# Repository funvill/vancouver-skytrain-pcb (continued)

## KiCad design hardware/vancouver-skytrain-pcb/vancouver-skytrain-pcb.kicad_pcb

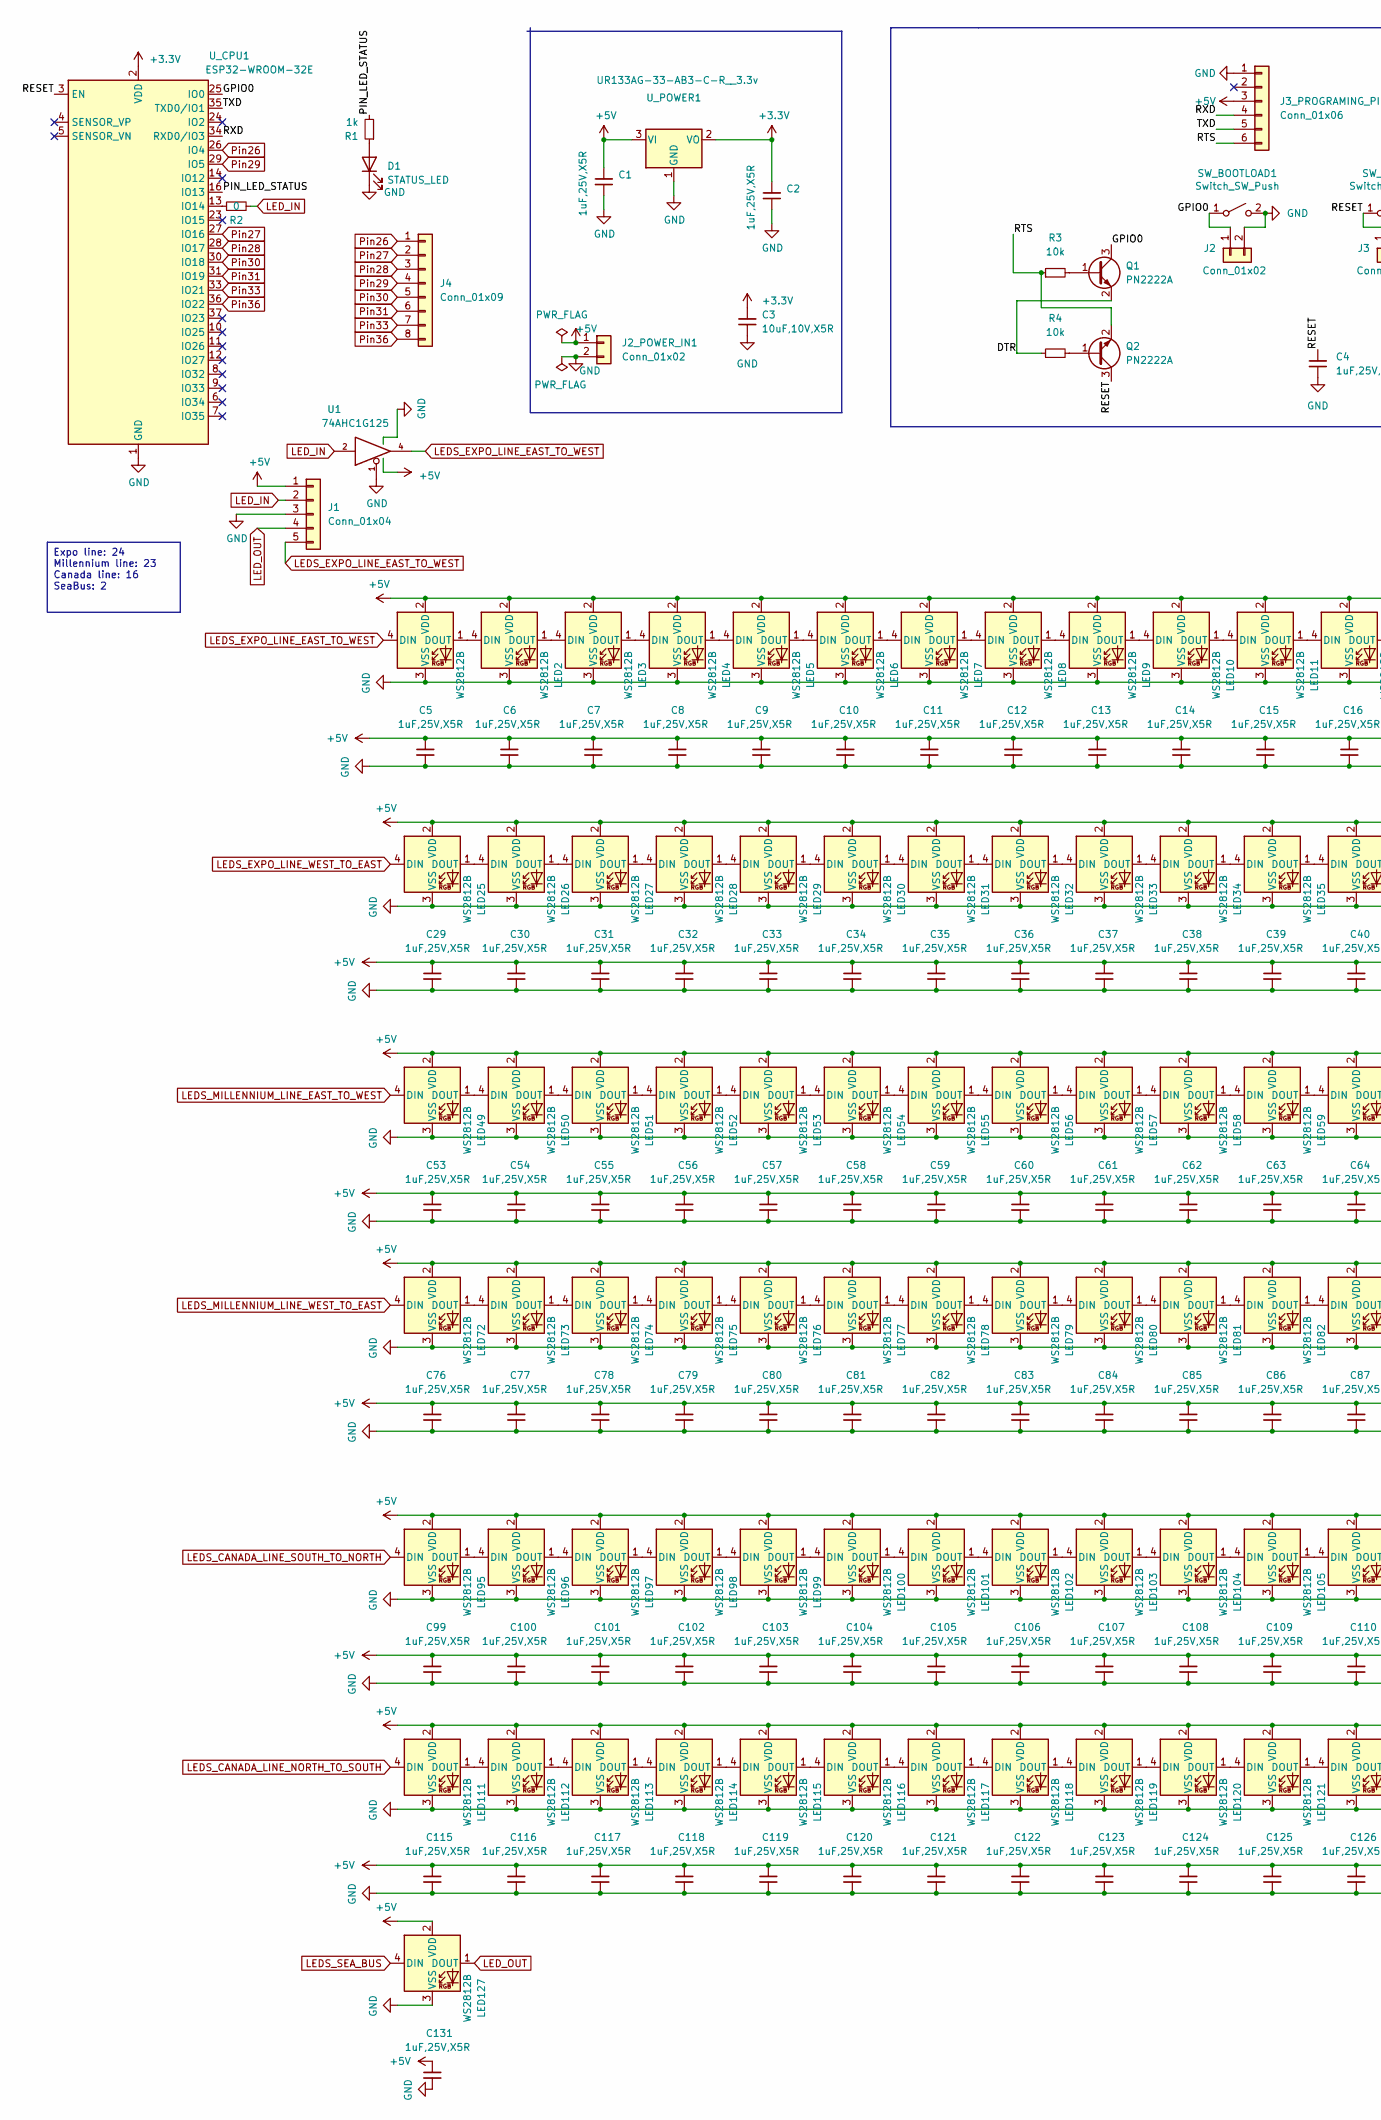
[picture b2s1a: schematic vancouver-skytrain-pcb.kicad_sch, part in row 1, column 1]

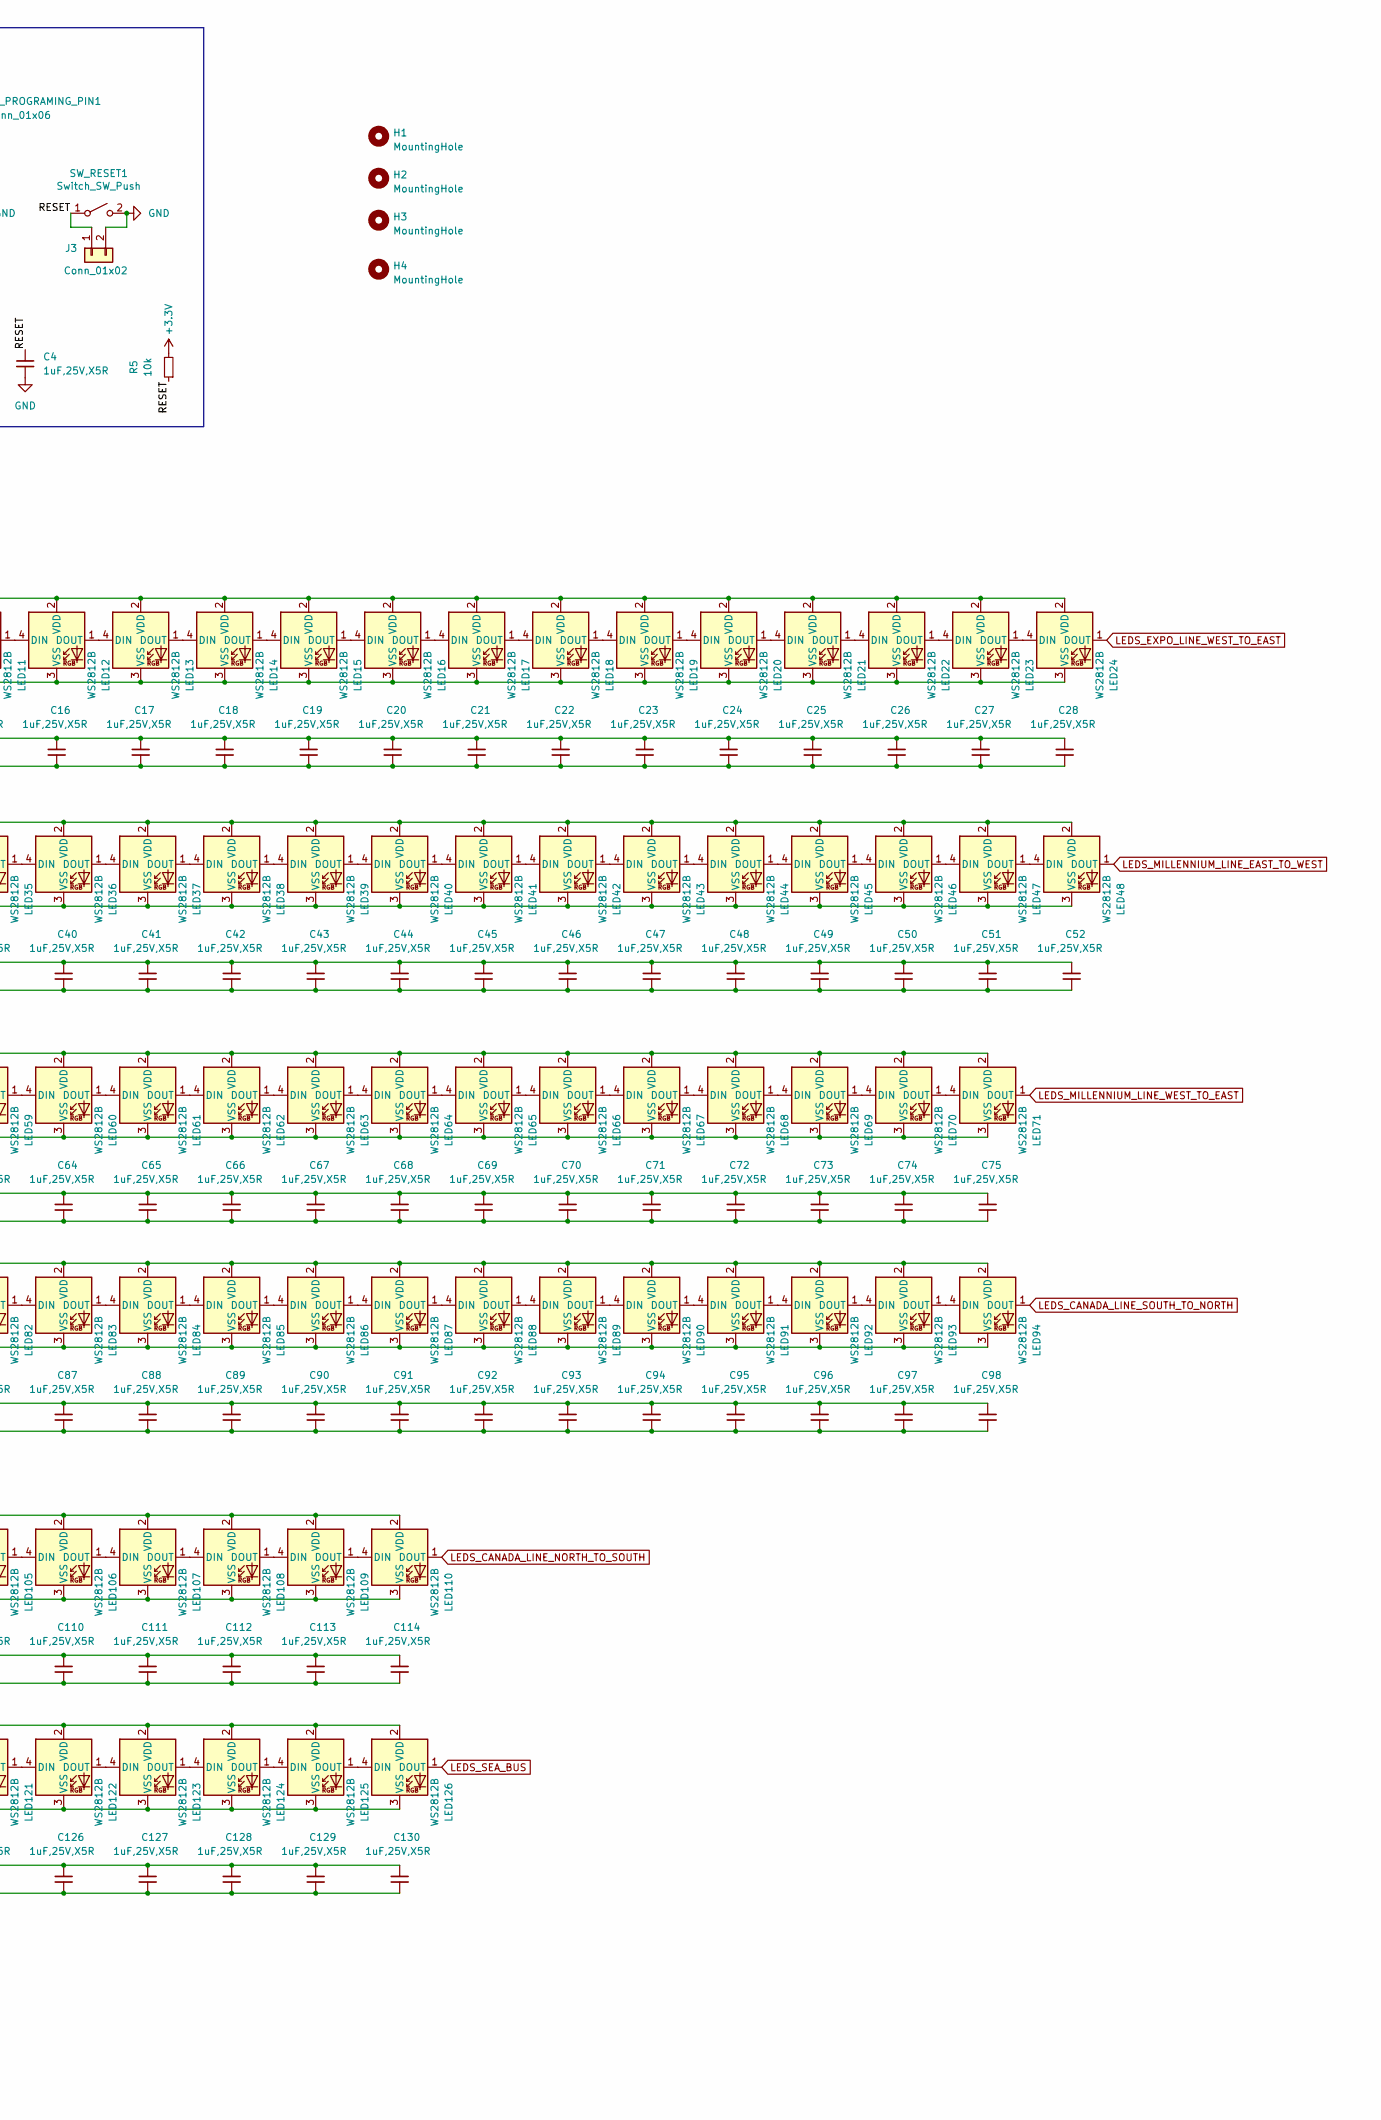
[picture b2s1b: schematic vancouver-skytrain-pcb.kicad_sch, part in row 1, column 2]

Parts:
C1, C2, C4, C5, C6, C7, C8, C9, C10, C11, C12, C13, C14, C15, C16, C17, C18, C19, C20, C21, C22, C23, C24, C25, C26, C27, C28, C29, C30, C31, C32, C33, C34, C35, C36, C37, C38, C39, C40, C41, C42, C43, C44, C45, C46, C47, C48, C49, C50, C51, C52, C53, C54, C55, C56, C57, C58, C59, C60, C61, C62, C63, C64, C65, C66, C67, C68, C69, C70, C71, C72, C73, C74, C75, C76, C77, C78, C79, C80, C81, C82, C83, C84, C85, C86, C87, C88, C89, C90, C91, C92, C93, C94, C95, C96, C97, C98, C99, C100, C101, C102, C103, C104, C105, C106, C107, C108, C109, C110, C111, C112, C113, C114, C115, C116, C117, C118, C119, C120, C121, C122, C123, C124, C125, C126, C127, C128, C129, C130, C131: 1uF,25V,X5R; C_0402_1005Metric; MFGPN CL05A105KA5NQNC; LCSC C52923
C3: 10uF,10V,X5R; C_0603_1608Metric; MFGPN CL10A106KP8NNNC; LCSC C19702
D1: STATUS_LED; LED_0603_1608Metric; LCSC C2286
H1, H2, H3, H4: MountingHole; MountingHole_3.2mm_M3
J1: Conn_01x04; PinHeader_1x05_P2.54mm_Vertical
J2, J3: Conn_01x02; PinHeader_1x02_P2.54mm_Vertical
J2_POWER_IN1: Conn_01x02; PhoenixContact_MCV_1,5_2-G-3.81_1x02_P3.81mm_Vertical
J3_PROGRAMING_PIN1: Conn_01x06; PinHeader_1x06_P2.54mm_Vertical
J4: Conn_01x09; PinHeader_1x08_P2.54mm_Vertical
LED1, LED2, LED3, LED4, LED5, LED6, LED7, LED8, LED9, LED10, LED11, LED12, LED13, LED14, LED15, LED16, LED17, LED18, LED19, LED20, LED21, LED22, LED23, LED24, LED25, LED26, LED27, LED28, LED29, LED30, LED31, LED32, LED33, LED34, LED35, LED36, LED37, LED38, LED39, LED40, LED41, LED42, LED43, LED44, LED45, LED46, LED47, LED48, LED49, LED50, LED51, LED52, LED53, LED54, LED55, LED56, LED57, LED58, LED59, LED60, LED61, LED62, LED63, LED64, LED65, LED66, LED67, LED68, LED69, LED70, LED71, LED72, LED73, LED74, LED75, LED76, LED77, LED78, LED79, LED80, LED81, LED82, LED83, LED84, LED85, LED86, LED87, LED88, LED89, LED90, LED91, LED92, LED93, LED94, LED95, LED96, LED97, LED98, LED99, LED100, LED101, LED102, LED103, LED104, LED105, LED106, LED107, LED108, LED109, LED110, LED111, LED112, LED113, LED114, LED115, LED116, LED117, LED118, LED119, LED120, LED121, LED122, LED123, LED124, LED125, LED126, LED127: WS2812B; XL-1010RGBC-WS2812B; LCSC C5349953
Q1, Q2: PN2222A; SOT-416; LCSC C242260
R1: 1k; C_0402_1005Metric; MFGPN 0402WGF1001TCE; LCSC C11702
R2: 0; R_0402_1005Metric; MFGPN 0402WGF0000TCE; LCSC C17168
R3, R4, R5: 10k; C_0402_1005Metric; MFGPN 0402WGF1002TCE; LCSC C25744
SW_BOOTLOAD1: Switch_SW_Push; SW_Push_1P1T_NO_6x6mm_H9.5mm; LCSC DNP
SW_RESET1: Switch_SW_Push; SW_Push_1P1T_NO_6x6mm_H9.5mm; LCSC DNP
U1: 74AHC1G125; SOT-23-5; LCSC C23654
U_CPU1: ESP32-WROOM-32E; ESP32-WROOM-32; LCSC C701342
U_POWER1: UR133AG-33-AB3-C-R__3.3v; SOT-89-3; LCSC C73288

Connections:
+3.3V: C2.1, C3.1, R5.2, U_CPU1.2 (VDD), U_POWER1.2 (VO)
+5V: C1.1, C5.1, C6.1, C7.1, C8.1, C9.1, C10.1, C11.1, C12.1, C13.1, C14.1, C15.1, C16.1, C17.1, C18.1, C19.1, C20.1, C21.1, C22.1, C23.1, C24.1, C25.1, C26.1, C27.1, C28.1, C29.1, C30.1, C31.1, C32.1, C33.1, C34.1, C35.1, C36.1, C37.1, C38.1, C39.1, C40.1, C41.1, C42.1, C43.1, C44.1, C45.1, C46.1, C47.1, C48.1, C49.1, C50.1, C51.1, C52.1, C53.1, C54.1, C55.1, C56.1, C57.1, C58.1, C59.1, C60.1, C61.1, C62.1, C63.1, C64.1, C65.1, C66.1, C67.1, C68.1, C69.1, C70.1, C71.1, C72.1, C73.1, C74.1, C75.1, C76.1, C77.1, C78.1, C79.1, C80.1, C81.1, C82.1, C83.1, C84.1, C85.1, C86.1, C87.1, C88.1, C89.1, C90.1, C91.1, C92.1, C93.1, C94.1, C95.1, C96.1, C97.1, C98.1, C99.1, C100.1, C101.1, C102.1, C103.1, C104.1, C105.1, C106.1, C107.1, C108.1, C109.1, C110.1, C111.1, C112.1, C113.1, C114.1, C115.1, C116.1, C117.1, C118.1, C119.1, C120.1, C121.1, C122.1, C123.1, C124.1, C125.1, C126.1, C127.1, C128.1, C129.1, C130.1, C131.1, J1.1, J2_POWER_IN1.1, J3_PROGRAMING_PIN1.3, LED1.2 (VDD), LED2.2 (VDD), LED3.2 (VDD), LED4.2 (VDD), LED5.2 (VDD), LED6.2 (VDD), LED7.2 (VDD), LED8.2 (VDD), LED9.2 (VDD), LED10.2 (VDD), LED11.2 (VDD), LED12.2 (VDD), LED13.2 (VDD), LED14.2 (VDD), LED15.2 (VDD), LED16.2 (VDD), LED17.2 (VDD), LED18.2 (VDD), LED19.2 (VDD), LED20.2 (VDD), LED21.2 (VDD), LED22.2 (VDD), LED23.2 (VDD), LED24.2 (VDD), LED25.2 (VDD), LED26.2 (VDD), LED27.2 (VDD), LED28.2 (VDD), LED29.2 (VDD), LED30.2 (VDD), LED31.2 (VDD), LED32.2 (VDD), LED33.2 (VDD), LED34.2 (VDD), LED35.2 (VDD), LED36.2 (VDD), LED37.2 (VDD), LED38.2 (VDD), LED39.2 (VDD), LED40.2 (VDD), LED41.2 (VDD), LED42.2 (VDD), LED43.2 (VDD), LED44.2 (VDD), LED45.2 (VDD), LED46.2 (VDD), LED47.2 (VDD), LED48.2 (VDD), LED49.2 (VDD), LED50.2 (VDD), LED51.2 (VDD), LED52.2 (VDD), LED53.2 (VDD), LED54.2 (VDD), LED55.2 (VDD), LED56.2 (VDD), LED57.2 (VDD), LED58.2 (VDD), LED59.2 (VDD), LED60.2 (VDD), LED61.2 (VDD), LED62.2 (VDD), LED63.2 (VDD), LED64.2 (VDD), LED65.2 (VDD), LED66.2 (VDD), LED67.2 (VDD), LED68.2 (VDD), LED69.2 (VDD), LED70.2 (VDD), LED71.2 (VDD), LED72.2 (VDD), LED73.2 (VDD), LED74.2 (VDD), LED75.2 (VDD), LED76.2 (VDD), LED77.2 (VDD), LED78.2 (VDD), LED79.2 (VDD), LED80.2 (VDD), LED81.2 (VDD), LED82.2 (VDD), LED83.2 (VDD), LED84.2 (VDD), LED85.2 (VDD), LED86.2 (VDD), LED87.2 (VDD), LED88.2 (VDD), LED89.2 (VDD), LED90.2 (VDD), LED91.2 (VDD), LED92.2 (VDD), LED93.2 (VDD), LED94.2 (VDD), LED95.2 (VDD), LED96.2 (VDD), LED97.2 (VDD), LED98.2 (VDD), LED99.2 (VDD), LED100.2 (VDD), LED101.2 (VDD), LED102.2 (VDD), LED103.2 (VDD), LED104.2 (VDD), LED105.2 (VDD), LED106.2 (VDD), LED107.2 (VDD), LED108.2 (VDD), LED109.2 (VDD), LED110.2 (VDD), LED111.2 (VDD), LED112.2 (VDD), LED113.2 (VDD), LED114.2 (VDD), LED115.2 (VDD), LED116.2 (VDD), LED117.2 (VDD), LED118.2 (VDD), LED119.2 (VDD), LED120.2 (VDD), LED121.2 (VDD), LED122.2 (VDD), LED123.2 (VDD), LED124.2 (VDD), LED125.2 (VDD), LED126.2 (VDD), LED127.2 (VDD), U1.5 (VCC), U_POWER1.3 (VI); also elsewhere on the board
/DTR: Q1.2 (E), R4.1
/GPIO0: J2.1, Q1.3 (C), SW_BOOTLOAD1.1 (A), U_CPU1.25 (IO0)
/PIN_LED_STATUS: R1.2, U_CPU1.16 (IO13)
/RESET: C4.1, J3.1, Q2.3 (C), R5.1, SW_RESET1.1 (A), U_CPU1.3 (EN)
/RTS: J3_PROGRAMING_PIN1.6, Q2.2 (E), R3.1
/RXD: J3_PROGRAMING_PIN1.4, U_CPU1.34 (RXD0/IO3)
/TXD: J3_PROGRAMING_PIN1.5, U_CPU1.35 (TXD0/IO1)
GND: C1.2, C2.2, C3.2, C4.2, C5.2, C6.2, C7.2, C8.2, C9.2, C10.2, C11.2, C12.2, C13.2, C14.2, C15.2, C16.2, C17.2, C18.2, C19.2, C20.2, C21.2, C22.2, C23.2, C24.2, C25.2, C26.2, C27.2, C28.2, C29.2, C30.2, C31.2, C32.2, C33.2, C34.2, C35.2, C36.2, C37.2, C38.2, C39.2, C40.2, C41.2, C42.2, C43.2, C44.2, C45.2, C46.2, C47.2, C48.2, C49.2, C50.2, C51.2, C52.2, C53.2, C54.2, C55.2, C56.2, C57.2, C58.2, C59.2, C60.2, C61.2, C62.2, C63.2, C64.2, C65.2, C66.2, C67.2, C68.2, C69.2, C70.2, C71.2, C72.2, C73.2, C74.2, C75.2, C76.2, C77.2, C78.2, C79.2, C80.2, C81.2, C82.2, C83.2, C84.2, C85.2, C86.2, C87.2, C88.2, C89.2, C90.2, C91.2, C92.2, C93.2, C94.2, C95.2, C96.2, C97.2, C98.2, C99.2, C100.2, C101.2, C102.2, C103.2, C104.2, C105.2, C106.2, C107.2, C108.2, C109.2, C110.2, C111.2, C112.2, C113.2, C114.2, C115.2, C116.2, C117.2, C118.2, C119.2, C120.2, C121.2, C122.2, C123.2, C124.2, C125.2, C126.2, C127.2, C128.2, C129.2, C130.2, C131.2, D1.1 (K), J1.3, J2.2, J2_POWER_IN1.2, J3.2, J3_PROGRAMING_PIN1.1, LED1.3 (VSS), LED2.3 (VSS), LED3.3 (VSS), LED4.3 (VSS), LED5.3 (VSS), LED6.3 (VSS), LED7.3 (VSS), LED8.3 (VSS), LED9.3 (VSS), LED10.3 (VSS), LED11.3 (VSS), LED12.3 (VSS), LED13.3 (VSS), LED14.3 (VSS), LED15.3 (VSS), LED16.3 (VSS), LED17.3 (VSS), LED18.3 (VSS), LED19.3 (VSS), LED20.3 (VSS), LED21.3 (VSS), LED22.3 (VSS), LED23.3 (VSS), LED24.3 (VSS), LED25.3 (VSS), LED26.3 (VSS), LED27.3 (VSS), LED28.3 (VSS), LED29.3 (VSS), LED30.3 (VSS), LED31.3 (VSS), LED32.3 (VSS), LED33.3 (VSS), LED34.3 (VSS), LED35.3 (VSS), LED36.3 (VSS), LED37.3 (VSS), LED38.3 (VSS), LED39.3 (VSS), LED40.3 (VSS), LED41.3 (VSS), LED42.3 (VSS), LED43.3 (VSS), LED44.3 (VSS), LED45.3 (VSS), LED46.3 (VSS), LED47.3 (VSS), LED48.3 (VSS), LED49.3 (VSS), LED50.3 (VSS), LED51.3 (VSS), LED52.3 (VSS), LED53.3 (VSS), LED54.3 (VSS), LED55.3 (VSS), LED56.3 (VSS), LED57.3 (VSS), LED58.3 (VSS), LED59.3 (VSS), LED60.3 (VSS), LED61.3 (VSS), LED62.3 (VSS), LED63.3 (VSS), LED64.3 (VSS), LED65.3 (VSS), LED66.3 (VSS), LED67.3 (VSS), LED68.3 (VSS), LED69.3 (VSS), LED70.3 (VSS), LED71.3 (VSS), LED72.3 (VSS), LED73.3 (VSS), LED74.3 (VSS), LED75.3 (VSS), LED76.3 (VSS), LED77.3 (VSS), LED78.3 (VSS), LED79.3 (VSS), LED80.3 (VSS), LED81.3 (VSS), LED82.3 (VSS), LED83.3 (VSS), LED84.3 (VSS), LED85.3 (VSS), LED86.3 (VSS), LED87.3 (VSS), LED88.3 (VSS), LED89.3 (VSS), LED90.3 (VSS), LED91.3 (VSS), LED92.3 (VSS), LED93.3 (VSS), LED94.3 (VSS), LED95.3 (VSS), LED96.3 (VSS), LED97.3 (VSS), LED98.3 (VSS), LED99.3 (VSS), LED100.3 (VSS), LED101.3 (VSS), LED102.3 (VSS), LED103.3 (VSS), LED104.3 (VSS), LED105.3 (VSS), LED106.3 (VSS), LED107.3 (VSS), LED108.3 (VSS), LED109.3 (VSS), LED110.3 (VSS), LED111.3 (VSS), LED112.3 (VSS), LED113.3 (VSS), LED114.3 (VSS), LED115.3 (VSS), LED116.3 (VSS), LED117.3 (VSS), LED118.3 (VSS), LED119.3 (VSS), LED120.3 (VSS), LED121.3 (VSS), LED122.3 (VSS), LED123.3 (VSS), LED124.3 (VSS), LED125.3 (VSS), LED126.3 (VSS), LED127.3 (VSS), SW_BOOTLOAD1.2 (B), SW_RESET1.2 (B), U1.1, U1.3 (GND), U_CPU1.1 (GND), U_CPU1.15 (GND), U_CPU1.38 (GND), U_CPU1.39 (GND), U_POWER1.1 (GND); also elsewhere on the board
LEDS_CANADA_LINE_NORTH_TO_SOUTH: LED110.1 (DOUT), LED111.4 (DIN)
LEDS_CANADA_LINE_SOUTH_TO_NORTH: LED94.1 (DOUT), LED95.4 (DIN)
LEDS_EXPO_LINE_EAST_TO_WEST: J1.5, LED1.4 (DIN), U1.4
LEDS_EXPO_LINE_WEST_TO_EAST: LED24.1 (DOUT), LED25.4 (DIN)
LEDS_MILLENNIUM_LINE_EAST_TO_WEST: LED48.1 (DOUT), LED49.4 (DIN)
LEDS_MILLENNIUM_LINE_WEST_TO_EAST: LED71.1 (DOUT), LED72.4 (DIN)
LEDS_SEA_BUS: LED126.1 (DOUT), LED127.4 (DIN)
LED_IN: J1.2, R2.2, U1.2
LED_OUT: J1.4, LED127.1 (DOUT)
unnamed: D1.2 (A), R1.1
unnamed: LED1.1 (DOUT), LED2.4 (DIN)
unnamed: LED2.1 (DOUT), LED3.4 (DIN)
unnamed: LED3.1 (DOUT), LED4.4 (DIN)
unnamed: LED4.1 (DOUT), LED5.4 (DIN)
unnamed: LED5.1 (DOUT), LED6.4 (DIN)
unnamed: LED6.1 (DOUT), LED7.4 (DIN)
unnamed: LED7.1 (DOUT), LED8.4 (DIN)
unnamed: LED8.1 (DOUT), LED9.4 (DIN)
unnamed: LED9.1 (DOUT), LED10.4 (DIN)
unnamed: LED10.1 (DOUT), LED11.4 (DIN)
unnamed: LED11.1 (DOUT), LED12.4 (DIN)
unnamed: LED12.1 (DOUT), LED13.4 (DIN)
unnamed: LED13.1 (DOUT), LED14.4 (DIN)
unnamed: LED14.1 (DOUT), LED15.4 (DIN)
unnamed: LED15.1 (DOUT), LED16.4 (DIN)
unnamed: LED16.1 (DOUT), LED17.4 (DIN)
unnamed: LED17.1 (DOUT), LED18.4 (DIN)
unnamed: LED18.1 (DOUT), LED19.4 (DIN)
unnamed: LED19.1 (DOUT), LED20.4 (DIN)
unnamed: LED20.1 (DOUT), LED21.4 (DIN)
unnamed: LED21.1 (DOUT), LED22.4 (DIN)
unnamed: LED22.1 (DOUT), LED23.4 (DIN)
unnamed: LED23.1 (DOUT), LED24.4 (DIN)
unnamed: LED25.1 (DOUT), LED26.4 (DIN)
unnamed: LED26.1 (DOUT), LED27.4 (DIN)
unnamed: LED27.1 (DOUT), LED28.4 (DIN)
unnamed: LED28.1 (DOUT), LED29.4 (DIN)
unnamed: LED29.1 (DOUT), LED30.4 (DIN)
unnamed: LED30.1 (DOUT), LED31.4 (DIN)
unnamed: LED31.1 (DOUT), LED32.4 (DIN)
unnamed: LED32.1 (DOUT), LED33.4 (DIN)
unnamed: LED33.1 (DOUT), LED34.4 (DIN)
unnamed: LED34.1 (DOUT), LED35.4 (DIN)
unnamed: LED35.1 (DOUT), LED36.4 (DIN)
unnamed: LED36.1 (DOUT), LED37.4 (DIN)
unnamed: LED37.1 (DOUT), LED38.4 (DIN)
unnamed: LED38.1 (DOUT), LED39.4 (DIN)
unnamed: LED39.1 (DOUT), LED40.4 (DIN)
unnamed: LED40.1 (DOUT), LED41.4 (DIN)
unnamed: LED41.1 (DOUT), LED42.4 (DIN)
unnamed: LED42.1 (DOUT), LED43.4 (DIN)
unnamed: LED43.1 (DOUT), LED44.4 (DIN)
unnamed: LED44.1 (DOUT), LED45.4 (DIN)
unnamed: LED45.1 (DOUT), LED46.4 (DIN)
unnamed: LED46.1 (DOUT), LED47.4 (DIN)
unnamed: LED47.1 (DOUT), LED48.4 (DIN)
unnamed: LED49.1 (DOUT), LED50.4 (DIN)
unnamed: LED50.1 (DOUT), LED51.4 (DIN)
unnamed: LED51.1 (DOUT), LED52.4 (DIN)
unnamed: LED52.1 (DOUT), LED53.4 (DIN)
unnamed: LED53.1 (DOUT), LED54.4 (DIN)
unnamed: LED54.1 (DOUT), LED55.4 (DIN)
unnamed: LED55.1 (DOUT), LED56.4 (DIN)
unnamed: LED56.1 (DOUT), LED57.4 (DIN)
unnamed: LED57.1 (DOUT), LED58.4 (DIN)
unnamed: LED58.1 (DOUT), LED59.4 (DIN)
unnamed: LED59.1 (DOUT), LED60.4 (DIN)
unnamed: LED60.1 (DOUT), LED61.4 (DIN)
unnamed: LED61.1 (DOUT), LED62.4 (DIN)
unnamed: LED62.1 (DOUT), LED63.4 (DIN)
unnamed: LED63.1 (DOUT), LED64.4 (DIN)
unnamed: LED64.1 (DOUT), LED65.4 (DIN)
unnamed: LED65.1 (DOUT), LED66.4 (DIN)
unnamed: LED66.1 (DOUT), LED67.4 (DIN)
unnamed: LED67.1 (DOUT), LED68.4 (DIN)
unnamed: LED68.1 (DOUT), LED69.4 (DIN)
unnamed: LED69.1 (DOUT), LED70.4 (DIN)
unnamed: LED70.1 (DOUT), LED71.4 (DIN)
unnamed: LED72.1 (DOUT), LED73.4 (DIN)
unnamed: LED73.1 (DOUT), LED74.4 (DIN)
unnamed: LED74.1 (DOUT), LED75.4 (DIN)
unnamed: LED75.1 (DOUT), LED76.4 (DIN)
unnamed: LED76.1 (DOUT), LED77.4 (DIN)
unnamed: LED77.1 (DOUT), LED78.4 (DIN)
unnamed: LED78.1 (DOUT), LED79.4 (DIN)
unnamed: LED79.1 (DOUT), LED80.4 (DIN)
unnamed: LED80.1 (DOUT), LED81.4 (DIN)
unnamed: LED81.1 (DOUT), LED82.4 (DIN)
unnamed: LED82.1 (DOUT), LED83.4 (DIN)
unnamed: LED83.1 (DOUT), LED84.4 (DIN)
unnamed: LED84.1 (DOUT), LED85.4 (DIN)
unnamed: LED85.1 (DOUT), LED86.4 (DIN)
unnamed: LED86.1 (DOUT), LED87.4 (DIN)
unnamed: LED87.1 (DOUT), LED88.4 (DIN)
unnamed: LED88.1 (DOUT), LED89.4 (DIN)
unnamed: LED89.1 (DOUT), LED90.4 (DIN)
unnamed: LED90.1 (DOUT), LED91.4 (DIN)
unnamed: LED91.1 (DOUT), LED92.4 (DIN)
unnamed: LED92.1 (DOUT), LED93.4 (DIN)
unnamed: LED93.1 (DOUT), LED94.4 (DIN)
unnamed: LED95.1 (DOUT), LED96.4 (DIN)
unnamed: LED96.1 (DOUT), LED97.4 (DIN)
unnamed: LED97.1 (DOUT), LED98.4 (DIN)
unnamed: LED98.1 (DOUT), LED99.4 (DIN)
unnamed: LED99.1 (DOUT), LED100.4 (DIN)
unnamed: LED100.1 (DOUT), LED101.4 (DIN)
unnamed: LED101.1 (DOUT), LED102.4 (DIN)
unnamed: LED102.1 (DOUT), LED103.4 (DIN)
unnamed: LED103.1 (DOUT), LED104.4 (DIN)
unnamed: LED104.1 (DOUT), LED105.4 (DIN)
unnamed: LED105.1 (DOUT), LED106.4 (DIN)
unnamed: LED106.1 (DOUT), LED107.4 (DIN)
unnamed: LED107.1 (DOUT), LED108.4 (DIN)
unnamed: LED108.1 (DOUT), LED109.4 (DIN)
unnamed: LED109.1 (DOUT), LED110.4 (DIN)
unnamed: LED111.1 (DOUT), LED112.4 (DIN)
unnamed: LED112.1 (DOUT), LED113.4 (DIN)
unnamed: LED113.1 (DOUT), LED114.4 (DIN)
unnamed: LED114.1 (DOUT), LED115.4 (DIN)
unnamed: LED115.1 (DOUT), LED116.4 (DIN)
unnamed: LED116.1 (DOUT), LED117.4 (DIN)
unnamed: LED117.1 (DOUT), LED118.4 (DIN)
unnamed: LED118.1 (DOUT), LED119.4 (DIN)
unnamed: LED119.1 (DOUT), LED120.4 (DIN)
unnamed: LED120.1 (DOUT), LED121.4 (DIN)
unnamed: LED121.1 (DOUT), LED122.4 (DIN)
unnamed: LED122.1 (DOUT), LED123.4 (DIN)
unnamed: LED123.1 (DOUT), LED124.4 (DIN)
unnamed: LED124.1 (DOUT), LED125.4 (DIN)
unnamed: LED125.1 (DOUT), LED126.4 (DIN)
unnamed: Q1.1 (B), R3.2
unnamed: Q2.1 (B), R4.2
unnamed: R2.1, U_CPU1.13 (IO14)
Pin26: J4.1, U_CPU1.26 (IO4)
Pin27: J4.2, U_CPU1.27 (IO16)
Pin28: J4.3, U_CPU1.28 (IO17)
Pin29: J4.4, U_CPU1.29 (IO5)
Pin30: J4.5, U_CPU1.30 (IO18)
Pin31: J4.6, U_CPU1.31 (IO19)
Pin33: J4.7, U_CPU1.33 (IO21)
Pin36: J4.8, U_CPU1.36 (IO22)

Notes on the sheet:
Expo line: 24 Millennium line: 23 Canada line: 16 SeaBus: 2

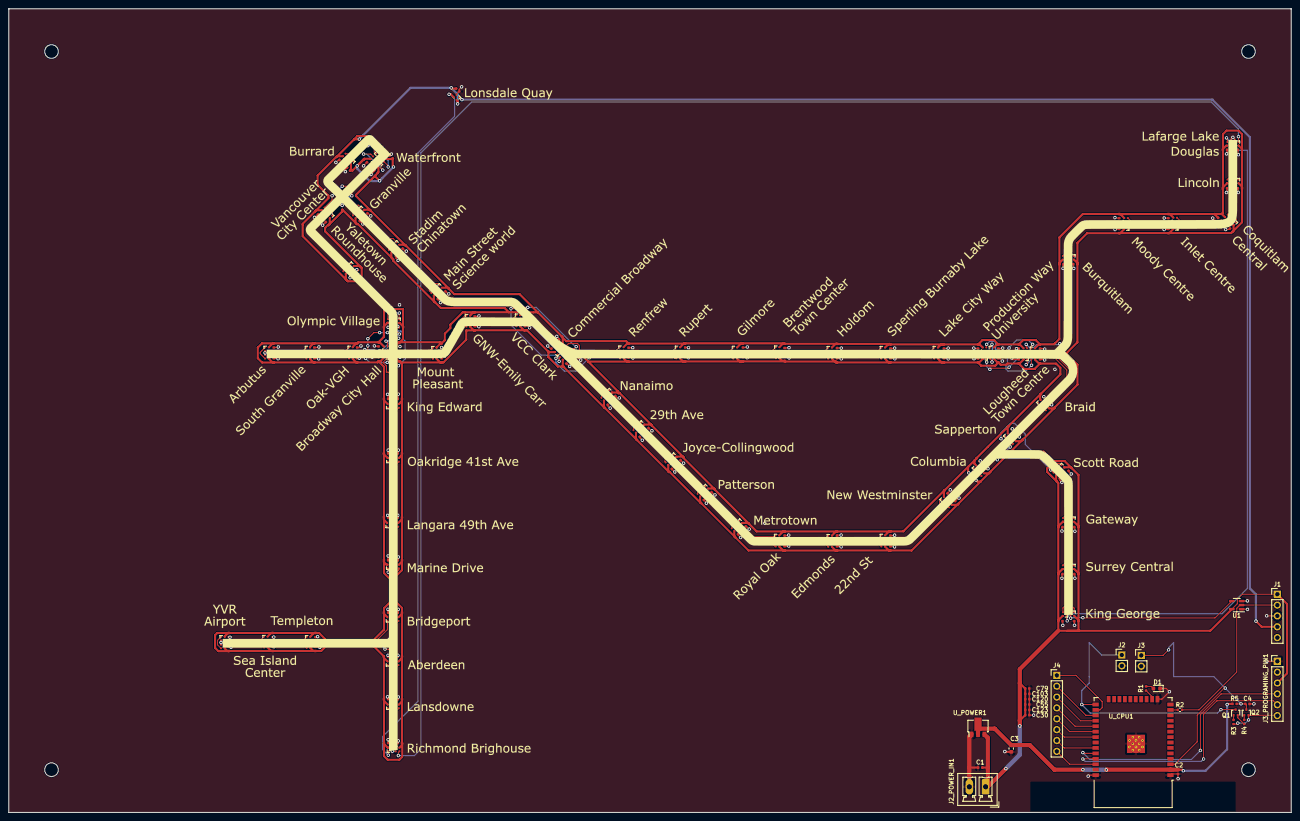
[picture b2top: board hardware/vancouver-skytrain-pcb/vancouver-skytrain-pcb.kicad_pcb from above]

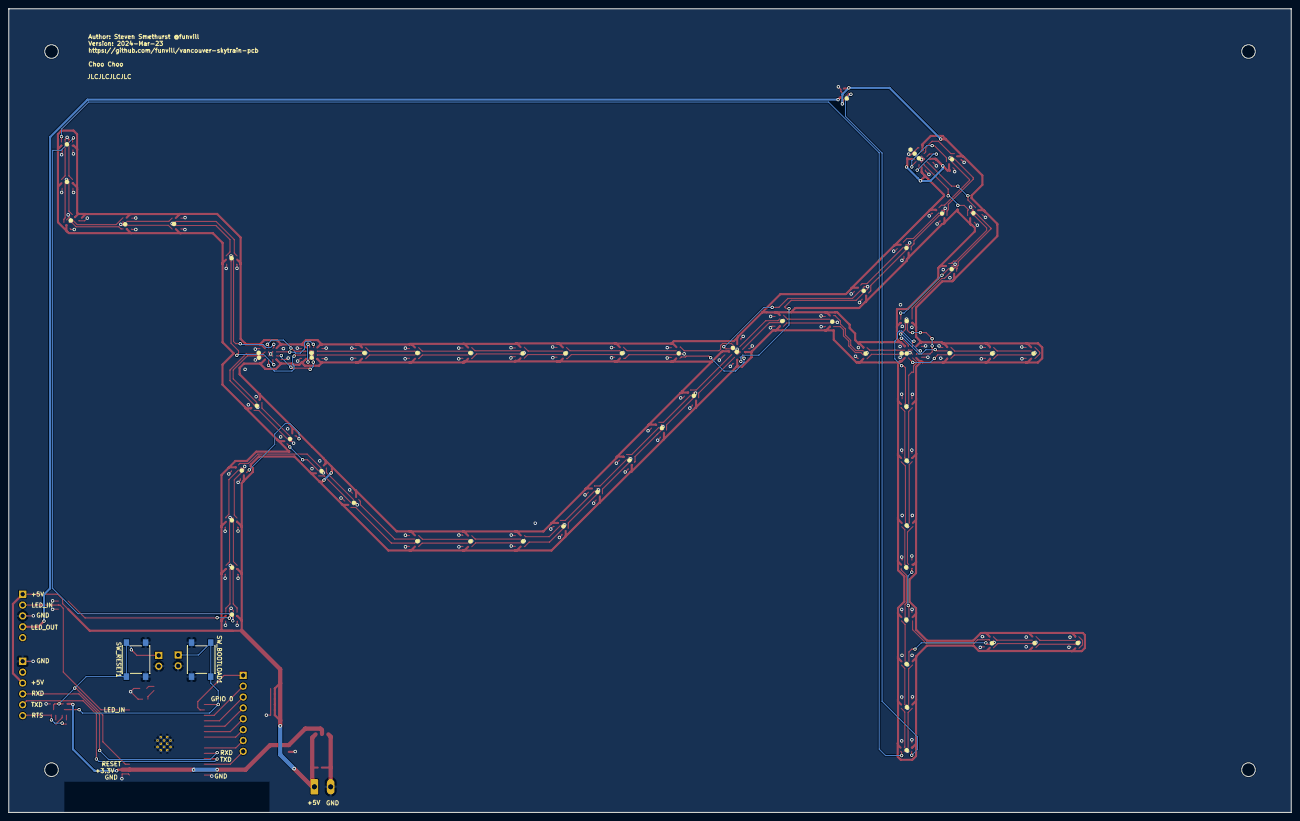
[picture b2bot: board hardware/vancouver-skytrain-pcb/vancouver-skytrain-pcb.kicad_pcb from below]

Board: 2 copper layers, 300.0 x 188.0 mm, 287 parts (2 on the bottom side), 151 nets.

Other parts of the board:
C132, C133, C134, C135, C136, C138: 1uF,25V,X5R; C_0402_1005Metric

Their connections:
+5V: C132.1, C133.1, C134.1, C135.1, C136.1, C138.1; also elsewhere on the board
GND: C132.2, C133.2, C134.2, C135.2, C136.2, C138.2; also elsewhere on the board

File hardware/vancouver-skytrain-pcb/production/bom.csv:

Designator,Footprint,Quantity,Value,LCSC Part #
"C1, C10, C100, C101, C102, C103, C104, C105, C106, C107, C108, C109, C11, C110, C111, C112, C113, C114, C115, C116, C117, C118, C119, C12, C120, C121, C122, C123, C124, C125, C126, C127, C128, C129, C13, C130, C131, C132, C133, C134, C135, C136, C138, C14, C15, C16, C17, C18, C19, C2, C20, C21, C22, C23, C24, C25, C26, C27, C28, C29, C30, C31, C32, C33, C34, C35, C36, C37, C38, C39, C4, C40, C41, C42, C43, C44, C45, C46, C47, C48, C49, C5, C50, C51, C52, C53, C54, C55, C56, C57, C58, C59, C6, C60, C61, C62, C63, C64, C65, C66, C67, C68, C69, C7, C70, C71, C72, C73, C74, C75, C76, C77, C78, C79, C8, C80, C81, C82, C83, C84, C85, C86, C87, C88, C89, C9, C90, C91, C92, C93, C94, C95, C96, C97, C98, C99",0402,136,"1uF,25V,X5R ",C52923
C3,0603,1,"10uF,10V,X5R ",C19702
D1,0603,1,STATUS_LED,C2286
"H1, H2, H3, H4",MountingHole_3.2mm_M3,4,MountingHole,
J1,PinHeader_1x05_P2.54mm_Vertical,1,Conn_01x04,
"J2, J3",PinHeader_1x02_P2.54mm_Vertical,2,Conn_01x02,
J2_POWER_IN1,"PhoenixContact_MCV_1,5_2-G-3.81_1x02_P3.81mm_Vertical",1,Conn_01x02,
J3_PROGRAMING_PIN1,PinHeader_1x06_P2.54mm_Vertical,1,Conn_01x06,
J4,PinHeader_1x08_P2.54mm_Vertical,1,Conn_01x09,
"LED1, LED10, LED100, LED101, LED102, LED103, LED104, LED105, LED106, LED107, LED108, LED109, LED11, LED110, LED111, LED112, LED113, LED114, LED115, LED116, LED117, LED118, LED119, LED12, LED120, LED121, LED122, LED123, LED124, LED125, LED126, LED127, LED13, LED14, LED15, LED16, LED17, LED18, LED19, LED2, LED20, LED21, LED22, LED23, LED24, LED25, LED26, LED27, LED28, LED29, LED3, LED30, LED31, LED32, LED33, LED34, LED35, LED36, LED37, LED38, LED39, LED4, LED40, LED41, LED42, LED43, LED44, LED45, LED46, LED47, LED48, LED49, LED5, LED50, LED51, LED52, LED53, LED54, LED55, LED56, LED57, LED58, LED59, LED6, LED60, LED61, LED62, LED63, LED64, LED65, LED66, LED67, LED68, LED69, LED7, LED70, LED71, LED72, LED73, LED74, LED75, LED76, LED77, LED78, LED79, LED8, LED80, LED81, LED82, LED83, LED84, LED85, LED86, LED87, LED88, LED89, LED9, LED90, LED91, LED92, LED93, LED94, LED95, LED96, LED97, LED98, LED99",XL-1010RGBC-WS2812B,127,WS2812B,C5349953
"Q1, Q2",SOT-416,2,PN2222A,C242260
R1,0402,1,1k,C11702
R2,0402,1,0,C17168
"R3, R4, R5",0402,3,10k,C25744
"SW_BOOTLOAD1, SW_RESET1",SW_Push_1P1T_NO_6x6mm_H9.5mm,2,Switch_SW_Push,DNP
U1,SOT-23-5,1,74AHC1G125,C23654
U_CPU1,ESP32-WROOM-32,1,ESP32-WROOM-32E,C701342
U_POWER1,SOT-89-3,1,UR133AG-33-AB3-C-R__3.3v,C73288

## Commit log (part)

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2023-06-03 updated readme, added input documents
2023-06-03 First very rough version to check the placement of everything
2023-06-04 positioned all the LEDs, Cap, and 5v Rails
2023-06-04 Ground pins
2023-06-05 Resolved a bunch of DRC errors
2023-06-05 Added images to the readme
2023-09-17 Clean up before sending to fab
2023-11-28 Added vancouver-skytrain-pcb - natrual
2024-03-23 Updated headers and update to kicad v8
2024-03-24 Added test points for all leds that look like bugs
2024-03-24 Updating the parts that are DNP
2024-03-25 Cleaning up before submitting
2024-06-20 Updated the firmware with demo mode for Teardown 2024
2024-06-20 Changed speeds
2025-02-07 Updated firmware to add more trains and better fading
2025-07-18 moved version 1 to the v1 folder
2025-11-29 Starting on version 2
2025-11-29 part placement
